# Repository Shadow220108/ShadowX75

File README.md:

# ShadowX75
It is a 75% layout, mechanical keyboard with hot-swap sockets! A rotatory encoder and an OLED screen!  

I made this project because I love keyboards. This would be my second keyboard after a split one! This version runs on QMK firmware and also has a rotatory encoder with an OLED screen  

### PCB
The PCB is designed to be compatible with Cherry MX switches and features hot-swappable kalih sockets.
| Schematics |
| --- |
|  | 

| PCB (All Layers)|
| --- |
|  |

| PCB (Without the art and zones)|
| --- |
|  |

| PS : Some PCB art|
| --- |
|  |
| --- |
|  |

## Case

The case is designed to be 3D printed and features a sandwich mount design with a 5° typing angle. The bottom case, top case, plate, and knob are all designed to be printed.

| Case Full|
| --- |
|  |

| Case Exploded View|
| --- |
|  |

## BOM ( I already have the parts mentioned as self sourced )
|Name                        |Purpose                                                       |Cost (USD)|Qty|Total (USD)                      |Link           |Distributor                                                        |
|----------------------------|--------------------------------------------------------------|----------|---|---------------------------------|---------------|-------------------------------------------------------------------|
|                            |                                                              |          |   |                                 |               |                                                                   |
|Hotswap sockets             |To solder to the PCB for switches                             |$0.11     |90 |$9.90                            |[Link to Listing](https://stackskb.com/store/gateron-hotswap-sockets/)|Stackskb                                                           |
|PCB ( 5 MOQ )               |this is the main circuit board for keyboard                   |$40.00    |1  |$40.00                           |-              |JLCPCB                                                             |
|Stabilzers                  |To support the 2u and 6.25u keys                              |$0.00     |1  |$0.00                            |-              |Self sourced ( I already have the parts mentioned as self sourced )|
|Heatset inserts and Screws  |To attach the 3 bodies together                               |$0.00     |8  |$0.00                            |-              |Self sourced                                                       |
|Rotatory Encoder            |To control volume/brightness                                  |$0.00     |1  |$0.00                            |-              |Self sourced                                                       |
|OLED ( 0.91 inch )          |To display random stuff while I type                          |$0.00     |1  |$0.00                            |-              |Self sourced                                                       |
|Shipping charges            |Shipping charge to get the 3d prints ( from #printing-legion )|$6.00     |1  |$6.00                            |-              |#printing-legion                                                   |
|Pin headers ( 1x40 )        |To solder the rpi pico to the PCB                             |$0.01     |1  |$0.01                            |[Link to Listing](https://robu.in/product/2-54mm-1x40-pin-male-single-row-straight-short-header-strip-pack-of-3/)|robu.in                                                            |
|raspberry pi pico           |This is the MCU of the keyboard                               |$4.50     |1  |$4.50                            |[Link to Listing](https://robu.in/product/raspberry-pi-pico/)|robu.in                                                            |
|1N4148W SOD-123 1206 Diode  |Used for the matrix wiring in the keyboard                    |$0.01     |100|$0.92                            |[Link to Listing](https://robu.in/product/1n4148w-sod-123-1206-diodereel-of-3000/)|robu.in                                                            |
|Keycap set ( Full Keyboard )|To add on the switches                                        |$14.14    |1  |$14.14                           |[Link to Listing](https://stackskb.com/store/veekos-gradient-keycaps-cherry-profile-135-keys/?attribute_pa_colour=rose-latte)|Stackskb                                                           |
|Switches                    |To press the keys                                             |$0.26     |90 |$23.40                           |[Link to Listing](https://stackskb.com/store/akko-piano-pro-switch-pack-of-45/)|Stackskb                                                           |
|                            |                                                              |          |   |                                 |               |                                                                   |
|                            |                                                              |          |   |Total Estimated Cost (USD):$98.87|               |                                                                   |

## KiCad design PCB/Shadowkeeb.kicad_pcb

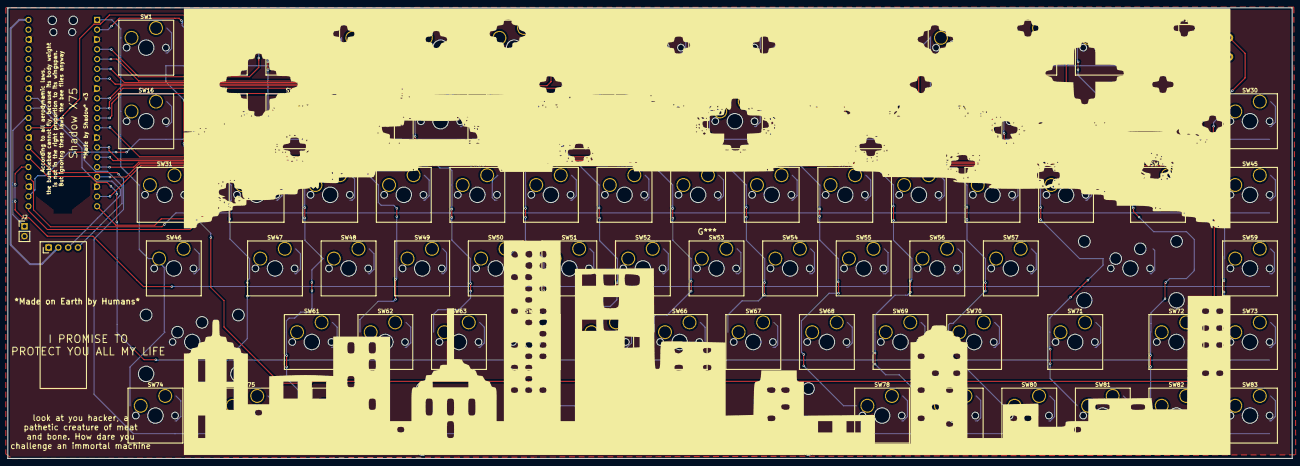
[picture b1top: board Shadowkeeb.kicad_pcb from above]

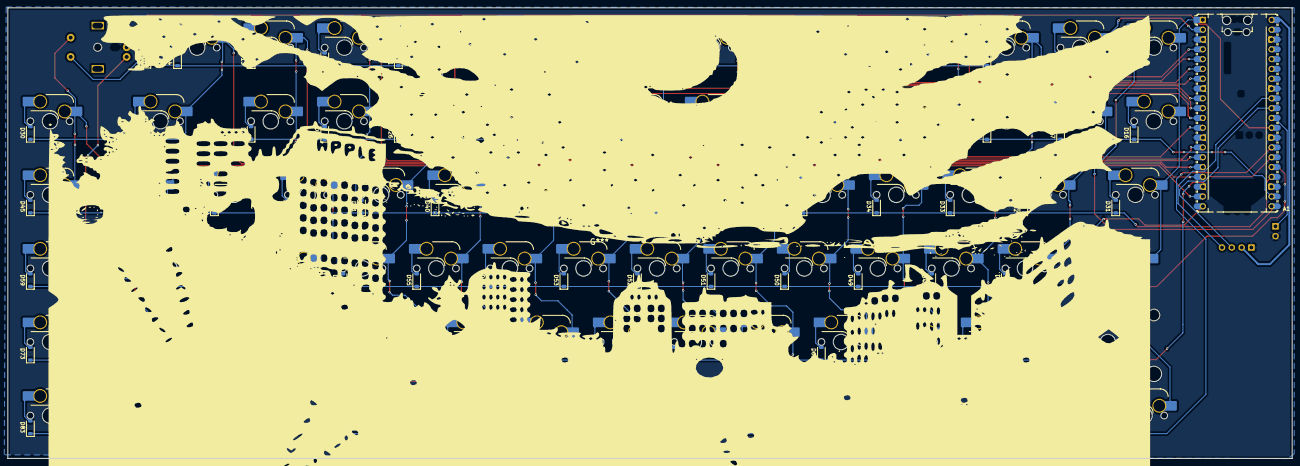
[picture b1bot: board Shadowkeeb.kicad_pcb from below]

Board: 2 copper layers, 332.5 x 116.7 mm, 169 parts (87 on the bottom side), 111 nets.

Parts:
A1: RaspberryPi_Pico; RaspberryPi_Pico_Common_Unspecified
D1, D2, D3, D4, D5, D6, D7, D8, D9, D10, D11, D12, D13, D14, D15, D16, D17, D18, D19, D20, D21, D22, D23, D24, D25, D26, D27, D28, D29, D30, D31, D32, D33, D34, D35, D36, D37, D38, D39, D40, D41, D42, D43, D44, D45, D46, D47, D48, D49, D50, D51, D52, D53, D54, D55, D56, D57, D58, D59, D60, D61, D62, D63, D64, D65, D66, D67, D68, D69, D70, D71, D72, D73, D74, D75, D76, D77, D78, D79, D80, D81, D82, D83: 1N4148; D_SOD-123
J2: Conn_01x02; PinHeader_1x02_P2.54mm_Vertical
SW1, SW2, SW3, SW4, SW5, SW6, SW7, SW8, SW9, SW10, SW11, SW12, SW13, SW14, SW16, SW17, SW18, SW19, SW20, SW21, SW22, SW23, SW24, SW25, SW26, SW27, SW28, SW30, SW32, SW33, SW34, SW35, SW36, SW37, SW38, SW39, SW40, SW41, SW42, SW43, SW45, SW47, SW48, SW49, SW50, SW51, SW52, SW53, SW54, SW55, SW56, SW57, SW59, SW61, SW62, SW63, SW64, SW65, SW66, SW67, SW68, SW69, SW70, SW72, SW73, SW74, SW75, SW76, SW78, SW79, SW80, SW81, SW82, SW83: SW_Push; SW_Hotswap_Kailh_MX_Plated_1.00u_With_Switch
SW15: RotaryEncoder_Switch; RotaryEncoder_Alps_EC11E-Switch_Vertical_H20mm_MountingHoles
SW29: SW_Push; SW_Hotswap_Kailh_MX_Plated_2.00u_With_Switch
SW31, SW44: SW_Push; SW_Hotswap_Kailh_MX_Plated_1.50u_With_Switch
SW46, SW71: SW_Push; SW_Hotswap_Kailh_MX_Plated_1.75u_With_Switch
SW58, SW60: SW_Push; MX-Hotswap-2.25U
SW77: SW_Push; MX-Hotswap-6.25U
U1: OLED_0.91_128x32

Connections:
+5V: A1.40 (VBUS), U1.2 (VCC)
/ADC0: A1.31 (GPIO26_ADC0), U1.3 (SCL)
/ADC1: A1.32 (GPIO27_ADC1), U1.4 (SDA)
/RUN: A1.30 (RUN), J2.1
/col1: A1.1 (GPIO0), SW1.1, SW16.1, SW31.1, SW46.1, SW60.1, SW74.1
/col2: A1.2 (GPIO1), SW2.1, SW17.1, SW32.1, SW47.1, SW75.1
/col3: A1.4 (GPIO2), SW3.1, SW18.1, SW33.1, SW48.1, SW61.1, SW76.1
/col4: A1.5 (GPIO3), SW4.1, SW19.1, SW34.1, SW49.1, SW62.1
/col5: A1.6 (GPIO4), SW5.1, SW20.1, SW35.1, SW50.1, SW63.1
/col6: A1.7 (GPIO5), SW6.1, SW21.1, SW36.1, SW51.1, SW64.1, SW77.1
/col7: A1.9 (GPIO6), SW7.1, SW22.1, SW37.1, SW52.1, SW65.1
/col8: A1.10 (GPIO7), SW8.1, SW23.1, SW38.1, SW53.1, SW66.1
/col9: A1.11 (GPIO8), SW9.1, SW24.1, SW39.1, SW54.1, SW67.1
/col10: A1.12 (GPIO9), SW10.1, SW25.1, SW40.1, SW55.1, SW68.1, SW78.1
/col11: A1.14 (GPIO10), SW11.1, SW26.1, SW41.1, SW56.1, SW69.1, SW79.1
/col12: A1.15 (GPIO11), SW12.1, SW27.1, SW42.1, SW57.1, SW70.1, SW80.1
/col13: A1.16 (GPIO12), SW13.1, SW28.1, SW43.1, SW58.1, SW71.1, SW81.1
/col14: A1.17 (GPIO13), SW14.1, SW29.1, SW44.1, SW72.1, SW82.1
/col15: A1.19 (GPIO14), SW15.S2, SW30.1, SW45.1, SW59.1, SW73.1, SW83.1
/encoderA: A1.29 (GPIO22), SW15.A
/encoderB: A1.20 (GPIO15), SW15.B
/row1: A1.21 (GPIO16), D1.1 (K), D2.1 (K), D3.1 (K), D4.1 (K), D5.1 (K), D6.1 (K), D7.1 (K), D8.1 (K), D9.1 (K), D10.1 (K), D11.1 (K), D12.1 (K), D13.1 (K), D14.1 (K), D15.1 (K)
/row2: A1.22 (GPIO17), D16.1 (K), D17.1 (K), D18.1 (K), D19.1 (K), D20.1 (K), D21.1 (K), D22.1 (K), D23.1 (K), D24.1 (K), D25.1 (K), D26.1 (K), D27.1 (K), D28.1 (K), D29.1 (K), D30.1 (K)
/row3: A1.24 (GPIO18), D31.1 (K), D32.1 (K), D33.1 (K), D34.1 (K), D35.1 (K), D36.1 (K), D37.1 (K), D38.1 (K), D39.1 (K), D40.1 (K), D41.1 (K), D42.1 (K), D43.1 (K), D44.1 (K), D45.1 (K)
/row4: A1.25 (GPIO19), D46.1 (K), D47.1 (K), D48.1 (K), D49.1 (K), D50.1 (K), D51.1 (K), D52.1 (K), D53.1 (K), D54.1 (K), D55.1 (K), D56.1 (K), D57.1 (K), D58.1 (K), D59.1 (K)
/row5: A1.26 (GPIO20), D60.1 (K), D61.1 (K), D62.1 (K), D63.1 (K), D64.1 (K), D65.1 (K), D66.1 (K), D67.1 (K), D68.1 (K), D69.1 (K), D70.1 (K), D71.1 (K), D72.1 (K), D73.1 (K)
/row6: A1.27 (GPIO21), D74.1 (K), D75.1 (K), D76.1 (K), D77.1 (K), D78.1 (K), D79.1 (K), D80.1 (K), D81.1 (K), D82.1 (K), D83.1 (K)
GND: A1.3 (GND), A1.8 (GND), A1.13 (GND), A1.18 (GND), A1.23 (GND), A1.28 (GND), A1.33 (AGND), A1.38 (GND), J2.2, SW15.C, U1.1 (GND)
unnamed: D1.2 (A), SW1.2
unnamed: D2.2 (A), SW2.2
unnamed: D3.2 (A), SW3.2
unnamed: D4.2 (A), SW4.2
unnamed: D5.2 (A), SW5.2
unnamed: D6.2 (A), SW6.2
unnamed: D7.2 (A), SW7.2
unnamed: D8.2 (A), SW8.2
unnamed: D9.2 (A), SW9.2
unnamed: D10.2 (A), SW10.2
unnamed: D11.2 (A), SW11.2
unnamed: D12.2 (A), SW12.2
unnamed: D13.2 (A), SW13.2
unnamed: D14.2 (A), SW14.2
unnamed: D15.2 (A), SW15.S1
unnamed: D16.2 (A), SW16.2
unnamed: D17.2 (A), SW17.2
unnamed: D18.2 (A), SW18.2
unnamed: D19.2 (A), SW19.2
unnamed: D20.2 (A), SW20.2
unnamed: D21.2 (A), SW21.2
unnamed: D22.2 (A), SW22.2
unnamed: D23.2 (A), SW23.2
unnamed: D24.2 (A), SW24.2
unnamed: D25.2 (A), SW25.2
unnamed: D26.2 (A), SW26.2
unnamed: D27.2 (A), SW27.2
unnamed: D28.2 (A), SW28.2
unnamed: D29.2 (A), SW29.2
unnamed: D30.2 (A), SW30.2
unnamed: D31.2 (A), SW31.2
unnamed: D32.2 (A), SW32.2
unnamed: D33.2 (A), SW33.2
unnamed: D34.2 (A), SW34.2
unnamed: D35.2 (A), SW35.2
unnamed: D36.2 (A), SW36.2
unnamed: D37.2 (A), SW37.2
unnamed: D38.2 (A), SW38.2
unnamed: D39.2 (A), SW39.2
unnamed: D40.2 (A), SW40.2
unnamed: D41.2 (A), SW41.2
unnamed: D42.2 (A), SW42.2
unnamed: D43.2 (A), SW43.2
unnamed: D44.2 (A), SW44.2
unnamed: D45.2 (A), SW45.2
unnamed: D46.2 (A), SW46.2
unnamed: D47.2 (A), SW47.2
unnamed: D48.2 (A), SW48.2
unnamed: D49.2 (A), SW49.2
unnamed: D50.2 (A), SW50.2
unnamed: D51.2 (A), SW51.2
unnamed: D52.2 (A), SW52.2
unnamed: D53.2 (A), SW53.2
unnamed: D54.2 (A), SW54.2
unnamed: D55.2 (A), SW55.2
unnamed: D56.2 (A), SW56.2
unnamed: D57.2 (A), SW57.2
unnamed: D58.2 (A), SW58.2
unnamed: D59.2 (A), SW59.2
unnamed: D60.2 (A), SW60.2
unnamed: D61.2 (A), SW61.2
unnamed: D62.2 (A), SW62.2
unnamed: D63.2 (A), SW63.2
unnamed: D64.2 (A), SW64.2
unnamed: D65.2 (A), SW65.2
unnamed: D66.2 (A), SW66.2
unnamed: D67.2 (A), SW67.2
unnamed: D68.2 (A), SW68.2
unnamed: D69.2 (A), SW69.2
unnamed: D70.2 (A), SW70.2
unnamed: D71.2 (A), SW71.2
unnamed: D72.2 (A), SW72.2
unnamed: D73.2 (A), SW73.2
unnamed: D74.2 (A), SW74.2
unnamed: D75.2 (A), SW75.2
unnamed: D76.2 (A), SW76.2
unnamed: D77.2 (A), SW77.2
unnamed: D78.2 (A), SW78.2
unnamed: D79.2 (A), SW79.2
unnamed: D80.2 (A), SW80.2
unnamed: D81.2 (A), SW81.2
unnamed: D82.2 (A), SW82.2
unnamed: D83.2 (A), SW83.2

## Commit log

2026-03-08 Uploading files from local repo
2026-03-08 Added images
2026-03-08 Added BOM.csv
